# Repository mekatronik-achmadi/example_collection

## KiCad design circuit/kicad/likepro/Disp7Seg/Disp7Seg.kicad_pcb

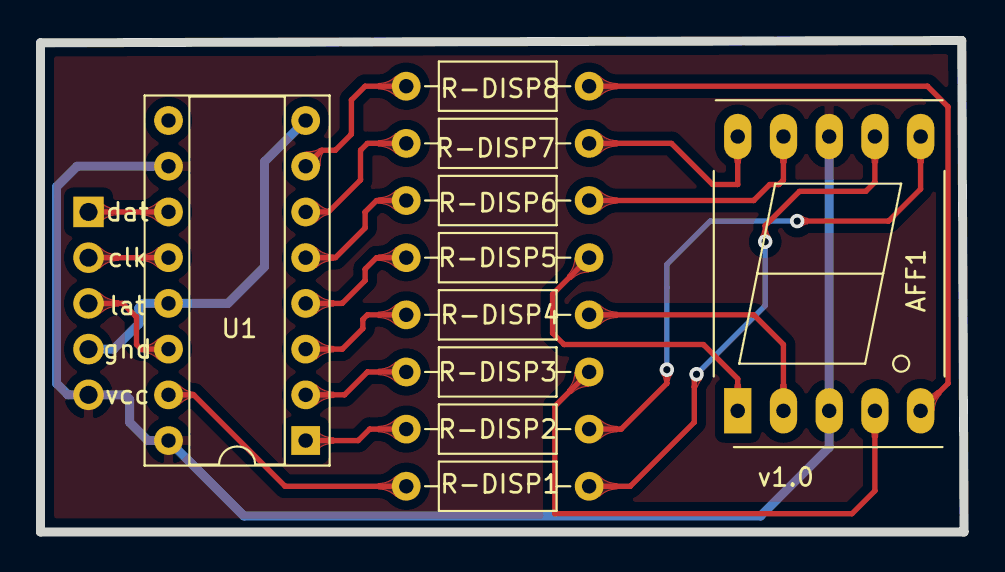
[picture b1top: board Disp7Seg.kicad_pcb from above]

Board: 2 copper layers, 51.3 x 27.3 mm, 11 parts (1 on the bottom side), 21 nets.

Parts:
AFF1: LTS-6960HR; 7SegmentLED_LTS6760_LTS6780
J-CONTROL1: Conn_01x05_Male; PinHeader_1x05_P2.54mm_Vertical
R-DISP1, R-DISP2, R-DISP3, R-DISP4, R-DISP5, R-DISP6, R-DISP7, R-DISP8: 220; R_Axial_DIN0207_L6.3mm_D2.5mm_P10.16mm_Horizontal
U1: 74HC595; DIP-16_W7.62mm_Socket

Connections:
/CLOCK: J-CONTROL1.2, U1.12
/DATA: J-CONTROL1.1, U1.11
/LATCH: J-CONTROL1.3, U1.14
/sgA: R-DISP1.2, U1.15
/sgB: R-DISP2.2, U1.1
/sgC: R-DISP3.2, U1.2
/sgD: R-DISP4.2, U1.3
/sgE: R-DISP5.2, U1.4
/sgF: R-DISP6.2, U1.5
/sgG: R-DISP7.2, U1.6
/sgH: R-DISP8.2, U1.7
GND: J-CONTROL1.4, U1.8, U1.13
unnamed: AFF1.1, R-DISP5.1
unnamed: AFF1.2, R-DISP4.1
unnamed: AFF1.4, R-DISP3.1
unnamed: AFF1.5, R-DISP8.1
unnamed: AFF1.6, R-DISP2.1
unnamed: AFF1.7, R-DISP1.1
unnamed: AFF1.9, R-DISP6.1
unnamed: AFF1.10, R-DISP7.1
VCC: AFF1.3, AFF1.8, J-CONTROL1.5, U1.10, U1.16

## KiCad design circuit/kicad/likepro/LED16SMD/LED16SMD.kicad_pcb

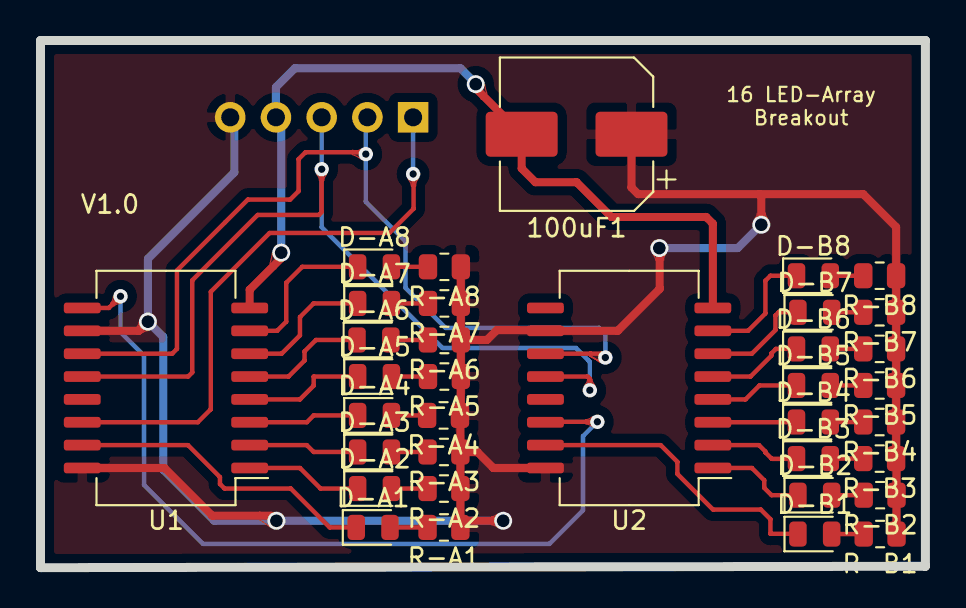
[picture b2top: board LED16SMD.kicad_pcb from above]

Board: 2 copper layers, 49.2 x 29.3 mm, 36 parts (1 on the bottom side), 38 nets.

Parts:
100uF1: CP; CP_Elec_8x5.4
D-A1, D-A2, D-A3, D-A4, D-A5, D-A6, D-A7, D-A8: LED; LED_0805_2012Metric
D-B1, D-B2, D-B3, D-B4, D-B5, D-B6, D-B7, D-B8: LED; LED_0805_2012Metric
J-CON1: Conn_01x05_Male; PinHeader_1x05_P2.54mm_Vertical
R-A1, R-A2, R-A3, R-A4, R-A5, R-A6, R-A7, R-A8: 220; R_0805_2012Metric
R-B1, R-B2, R-B3, R-B4, R-B5, R-B6, R-B7, R-B8: 220; R_0805_2012Metric
U1, U2: 74HC595; SOIC-16W_7.5x12.8mm_P1.27mm

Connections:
/CLOCK: J-CON1.2, U1.11, U2.11
/DATA: J-CON1.1, U1.14
/DATA_S: U1.9, U2.14
/LATCH: J-CON1.3, U1.12, U2.12
/saa: D-A1.1, U1.15
/sab: D-A2.1, U1.1
/sac: D-A3.1, U1.2
/sad: D-A4.1, U1.3
/sae: D-A5.1, U1.4
/saf: D-A6.1, U1.5
/sag: D-A7.1, U1.6
/sah: D-A8.1, U1.7
/sba: D-B1.1, U2.15
/sbb: D-B2.1, U2.1
/sbc: D-B3.1, U2.2
/sbd: D-B4.1, U2.3
/sbe: D-B5.1, U2.4
/sbf: D-B6.1, U2.5
/sbg: D-B7.1, U2.6
/sbh: D-B8.1, U2.7
GND: 100uF1.2, J-CON1.4, U1.8, U2.8
unnamed: D-A1.2, R-A1.2
unnamed: D-A2.2, R-A2.2
unnamed: D-A3.2, R-A3.2
unnamed: D-A4.2, R-A4.2
unnamed: D-A5.2, R-A5.2
unnamed: D-A6.2, R-A6.2
unnamed: D-A7.2, R-A7.2
unnamed: D-A8.2, R-A8.2
unnamed: D-B1.2, R-B1.2
unnamed: D-B2.2, R-B2.2
unnamed: D-B3.2, R-B3.2
unnamed: D-B4.2, R-B4.2
unnamed: D-B5.2, R-B5.2
unnamed: D-B6.2, R-B6.2
unnamed: D-B7.2, R-B7.2
unnamed: D-B8.2, R-B8.2
VCC: 100uF1.1, J-CON1.5, R-A1.1, R-A2.1, R-A3.1, R-A4.1, R-A5.1, R-A6.1, R-A7.1, R-A8.1, R-B1.1, R-B2.1, R-B3.1, R-B4.1, R-B5.1, R-B6.1, R-B7.1, R-B8.1, U1.10, U1.16, U2.10, U2.16

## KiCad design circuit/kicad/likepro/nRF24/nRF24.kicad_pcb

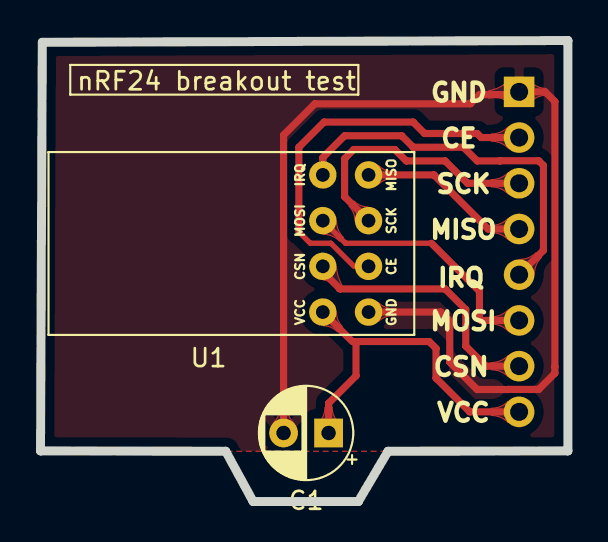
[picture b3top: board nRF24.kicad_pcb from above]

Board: 2 copper layers, 29.3 x 25.6 mm, 3 parts (1 on the bottom side), 8 nets.

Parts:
C1: 100nF; CP_Radial_D5.0mm_P2.50mm
J1: Conn_01x08_Male; PinHeader_1x08_P2.54mm_Vertical
U1: nnRF24

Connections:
/CE: J1.2, U1.1
/CSN: J1.7, U1.6
/IRQ: J1.5, U1.4
/MISO: J1.4, U1.3
/MOSI: J1.6, U1.5
/SCK: J1.3, U1.2
GND: C1.2, J1.1, U1.0
VCC: C1.1, J1.8, U1.7

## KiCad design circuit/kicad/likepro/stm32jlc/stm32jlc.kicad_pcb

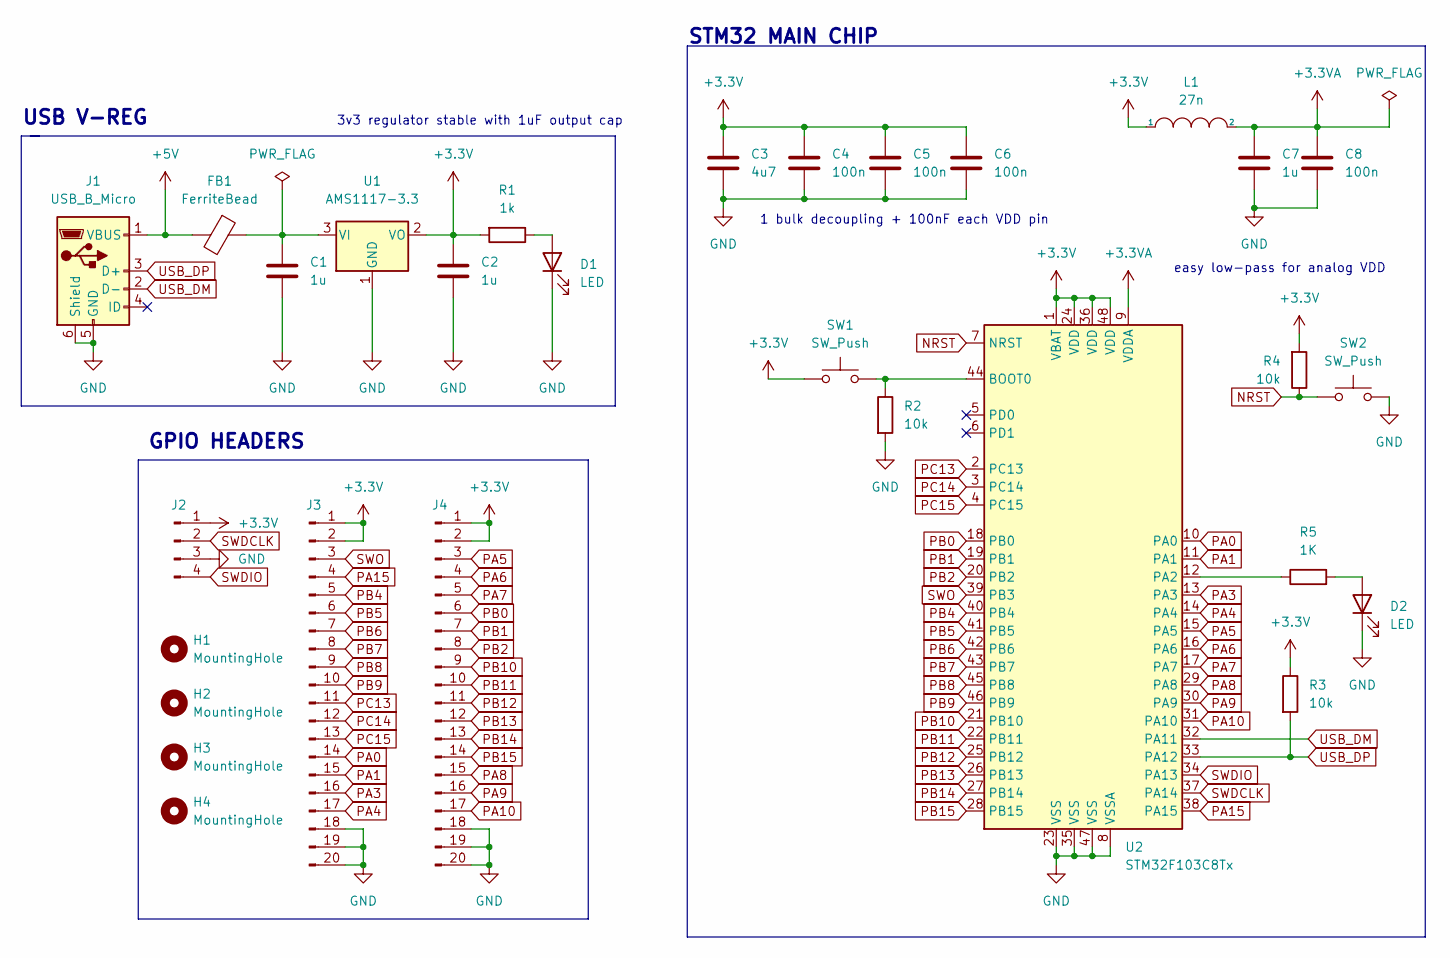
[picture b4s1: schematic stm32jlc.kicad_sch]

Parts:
C1, C2, C7: 1u; C_0805_2012Metric_Pad1.18x1.45mm_HandSolder
C3: 4u7; C_0805_2012Metric_Pad1.18x1.45mm_HandSolder
C4, C5, C6, C8: 100n; C_0805_2012Metric_Pad1.18x1.45mm_HandSolder
D1, D2: LED; LED_0805_2012Metric_Pad1.15x1.40mm_HandSolder
FB1: FerriteBead; L_0805_2012Metric_Pad1.05x1.20mm_HandSolder
H1, H2, H3, H4: MountingHole; MountingHole_2.5mm_Pad
J1: USB_B_Micro; USB_Micro-B_Wuerth_629105150521
J2: Conn_01x04_Male; PinHeader_1x04_P2.54mm_Vertical
J3, J4: Conn_01x20_Male; PinHeader_1x20_P2.54mm_Vertical
L1: 27n; L_0805_2012Metric_Pad1.05x1.20mm_HandSolder
R1: 1k; R_0805_2012Metric_Pad1.20x1.40mm_HandSolder
R2, R3, R4: 10k; R_0805_2012Metric_Pad1.20x1.40mm_HandSolder
R5: 1K; R_0805_2012Metric_Pad1.20x1.40mm_HandSolder
SW1, SW2: SW_Push; SW_PUSH_6mm
U1: AMS1117-3.3; SOT-223-3_TabPin2
U2: STM32F103C8Tx; LQFP-48_7x7mm_P0.5mm

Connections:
+3.3V: C2.1, C3.1, C4.1, C5.1, C6.1, J2.1, J3.1, J3.2, J4.1, J4.2, L1.1, R1.2, R3.1, R4.2, SW1.1, U1.2 (VO), U2.1 (VBAT), U2.24 (VDD), U2.36 (VDD), U2.48 (VDD)
+3.3VA: C7.1, C8.1, L1.2, U2.9 (VDDA)
+5V: FB1.2, J1.1 (VBUS)
GND: C1.2, C2.2, C3.2, C4.2, C5.2, C6.2, C7.2, C8.2, D1.1 (K), D2.1 (K), J1.5 (GND), J1.6 (Shield), J2.3, J3.18, J3.19, J3.20, J4.18, J4.19, J4.20, R2.2, SW2.1, U1.1 (GND), U2.8 (VSSA), U2.23 (VSS), U2.35 (VSS), U2.47 (VSS)
NRST: R4.1, SW2.2, U2.7 (NRST)
unnamed: C1.1, FB1.1, U1.3 (VI)
unnamed: D1.2 (A), R1.1
unnamed: D2.2 (A), R5.2
unnamed: R2.1, SW1.2, U2.44 (BOOT0)
unnamed: R5.1, U2.12 (PA2)
PA0: J3.14, U2.10 (PA0)
PA1: J3.15, U2.11 (PA1)
PA3: J3.16, U2.13 (PA3)
PA4: J3.17, U2.14 (PA4)
PA5: J4.3, U2.15 (PA5)
PA6: J4.4, U2.16 (PA6)
PA7: J4.5, U2.17 (PA7)
PA8: J4.15, U2.29 (PA8)
PA9: J4.16, U2.30 (PA9)
PA10: J4.17, U2.31 (PA10)
PA15: J3.4, U2.38 (PA15)
PB0: J4.6, U2.18 (PB0)
PB1: J4.7, U2.19 (PB1)
PB2: J4.8, U2.20 (PB2)
PB4: J3.5, U2.40 (PB4)
PB5: J3.6, U2.41 (PB5)
PB6: J3.7, U2.42 (PB6)
PB7: J3.8, U2.43 (PB7)
PB8: J3.9, U2.45 (PB8)
PB9: J3.10, U2.46 (PB9)
PB10: J4.9, U2.21 (PB10)
PB11: J4.10, U2.22 (PB11)
PB12: J4.11, U2.25 (PB12)
PB13: J4.12, U2.26 (PB13)
PB14: J4.13, U2.27 (PB14)
PB15: J4.14, U2.28 (PB15)
PC13: J3.11, U2.2 (PC13)
PC14: J3.12, U2.3 (PC14)
PC15: J3.13, U2.4 (PC15)
SWDCLK: J2.2, U2.37 (PA14)
SWDIO: J2.4, U2.34 (PA13)
SWO: J3.3, U2.39 (PB3)
USB_DM: J1.2 (D-), U2.32 (PA11)
USB_DP: J1.3 (D+), R3.2, U2.33 (PA12)

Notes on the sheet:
3v3 regulator stable with 1uF output cap
1 bulk decoupling + 100nF each VDD pin
STM32 MAIN CHIP
USB V-REG
easy low-pass for analog VDD
GPIO HEADERS

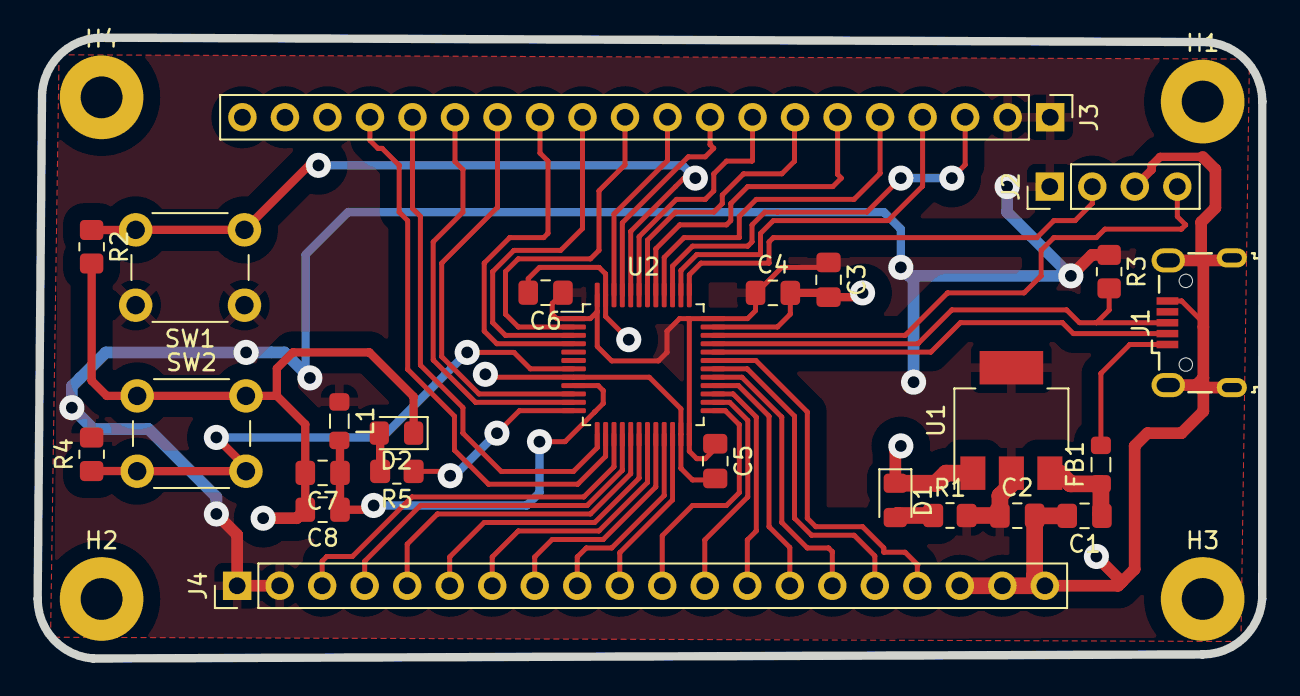
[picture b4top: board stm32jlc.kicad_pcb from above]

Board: 2 copper layers, 73.2 x 37.1 mm, 29 parts (0 on the bottom side), 44 nets.

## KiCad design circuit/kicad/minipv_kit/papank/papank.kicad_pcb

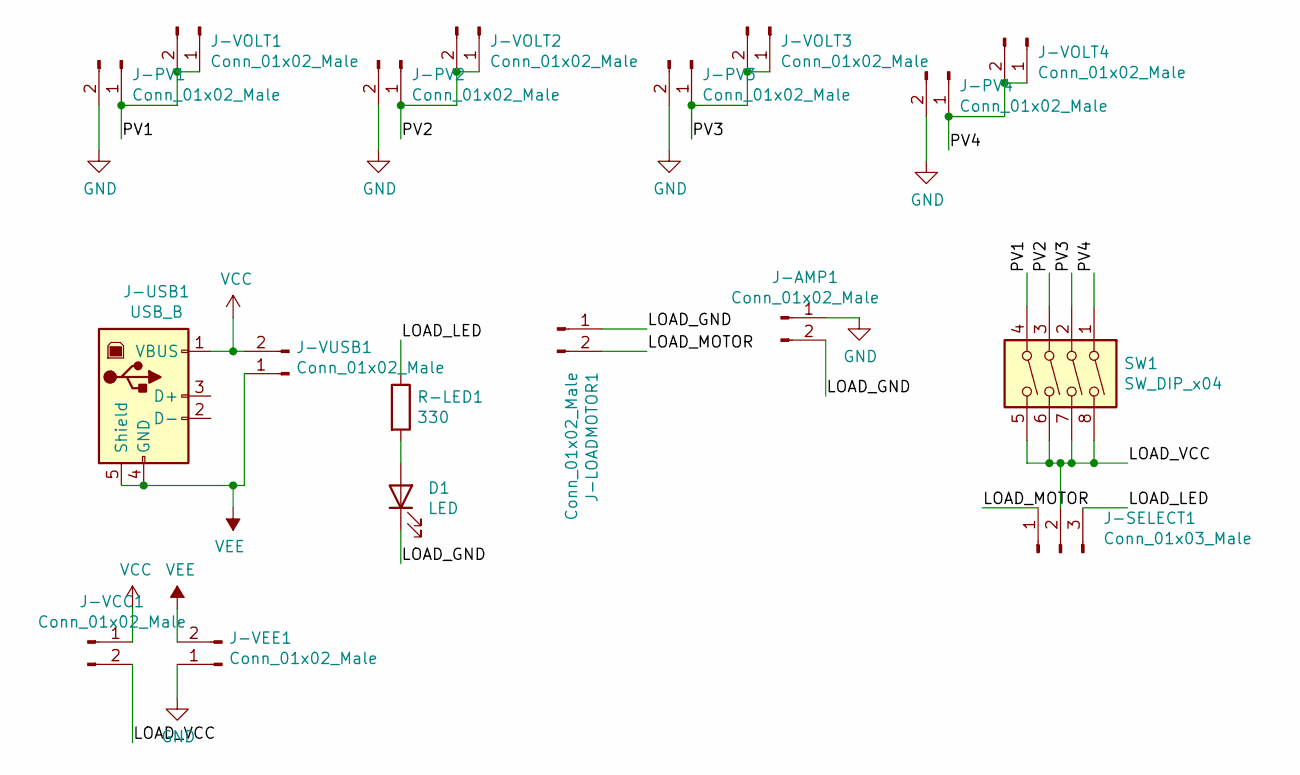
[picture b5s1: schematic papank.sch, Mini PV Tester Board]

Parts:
D1: LED; LED_D5.0mm
J-AMP1: Conn_01x02_Male; Molex_KK-254_AE-6410-02A_1x02_P2.54mm_Vertical
J-LOADMOTOR1: Conn_01x02_Male; Molex_KK-254_AE-6410-02A_1x02_P2.54mm_Vertical
J-PV1, J-PV2, J-PV3, J-PV4: Conn_01x02_Male; Molex_KK-254_AE-6410-02A_1x02_P2.54mm_Vertical
J-SELECT1: Conn_01x03_Male; PinHeader_1x03_P2.54mm_Vertical
J-USB1: USB_B; USB_B_Lumberg_2411_02_Horizontal
J-VCC1: Conn_01x02_Male; PinHeader_1x02_P2.54mm_Vertical
J-VEE1: Conn_01x02_Male; PinHeader_1x02_P2.54mm_Vertical
J-VOLT1, J-VOLT2, J-VOLT3, J-VOLT4: Conn_01x02_Male; PinHeader_1x02_P2.54mm_Vertical
J-VUSB1: Conn_01x02_Male; PinHeader_1x02_P2.54mm_Vertical
R-LED1: 330; R_Axial_DIN0207_L6.3mm_D2.5mm_P10.16mm_Horizontal
SW1: SW_DIP_x04; SW_DIP_SPSTx04_Slide_9.78x12.34mm_W7.62mm_P2.54mm

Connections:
/LOAD_GND: D1.1 (K), J-AMP1.2, J-LOADMOTOR1.1
/LOAD_LED: J-SELECT1.3, R-LED1.1
/LOAD_MOTOR: J-LOADMOTOR1.2, J-SELECT1.1
/LOAD_VCC: J-SELECT1.2, J-VCC1.2, SW1.5, SW1.6, SW1.7, SW1.8
/PV1: J-PV1.1, J-VOLT1.1, J-VOLT1.2, SW1.4
/PV2: J-PV2.1, J-VOLT2.1, J-VOLT2.2, SW1.3
/PV3: J-PV3.1, J-VOLT3.1, J-VOLT3.2, SW1.2
/PV4: J-PV4.1, J-VOLT4.1, J-VOLT4.2, SW1.1
GND: J-AMP1.1, J-PV1.2, J-PV2.2, J-PV3.2, J-PV4.2, J-VEE1.1
unnamed: D1.2 (A), R-LED1.2
VCC: J-USB1.1 (VBUS), J-VCC1.1, J-VUSB1.2
VEE: J-USB1.4 (GND), J-USB1.5 (Shield), J-VEE1.2, J-VUSB1.1

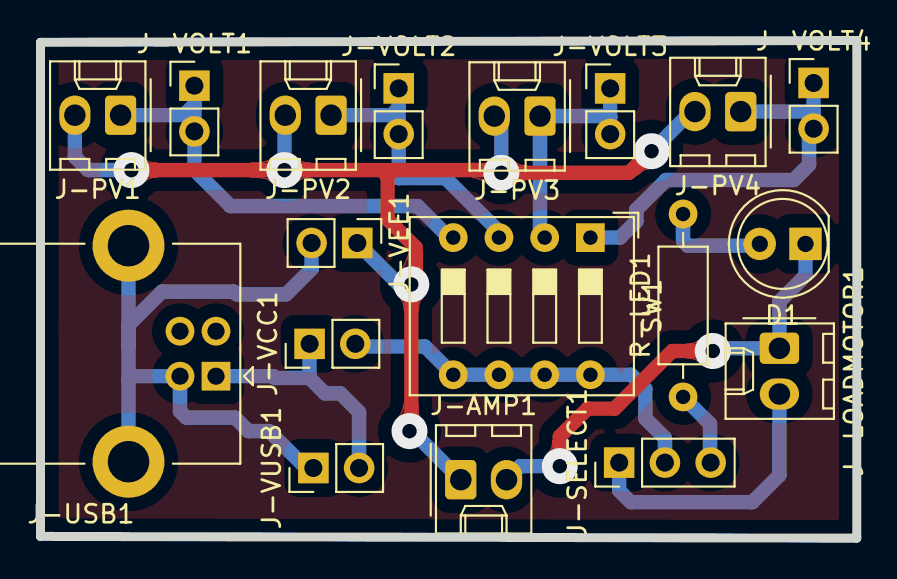
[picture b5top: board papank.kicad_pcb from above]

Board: 2 copper layers, 45.3 x 27.7 mm, 18 parts (0 on the bottom side), 12 nets.

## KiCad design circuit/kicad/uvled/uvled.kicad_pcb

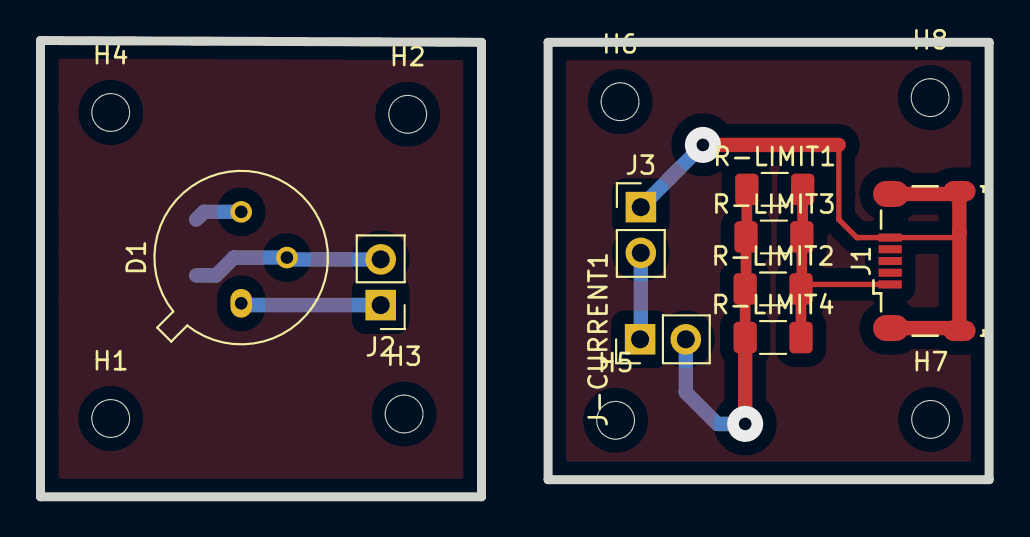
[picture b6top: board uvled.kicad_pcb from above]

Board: 2 copper layers, 52.7 x 25.4 mm, 18 parts (1 on the bottom side), 5 nets.

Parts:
D1: LED_PAD; TO-39-3
H1, H2, H3, H4, H5, H6, H7, H8: MountingHole; MountingHole_2.1mm
J1: USB_B_Micro; MicroUSB
J2, J3: Conn_01x02_Male; PinHeader_1x02_P2.54mm_Vertical
J-CURRENT1: Conn_01x02_Male; PinHeader_1x02_P2.54mm_Vertical
R-GND1: 0; R_1206_3216Metric_Pad1.30x1.75mm_HandSolder
R-LIMIT1, R-LIMIT2, R-LIMIT3, R-LIMIT4: 10K; R_1206_3216Metric_Pad1.30x1.75mm_HandSolder

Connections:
/VLED: D1.1, J2.1, J3.2, J-CURRENT1.1
GND: D1.2, J1.5, J1.6, J2.2, J3.1, R-GND1.2
unnamed: D1.3, R-GND1.1
unnamed: J-CURRENT1.2, R-LIMIT1.1, R-LIMIT2.1, R-LIMIT3.1, R-LIMIT4.1
VCC: J1.1, R-LIMIT1.2, R-LIMIT2.2, R-LIMIT3.2, R-LIMIT4.2

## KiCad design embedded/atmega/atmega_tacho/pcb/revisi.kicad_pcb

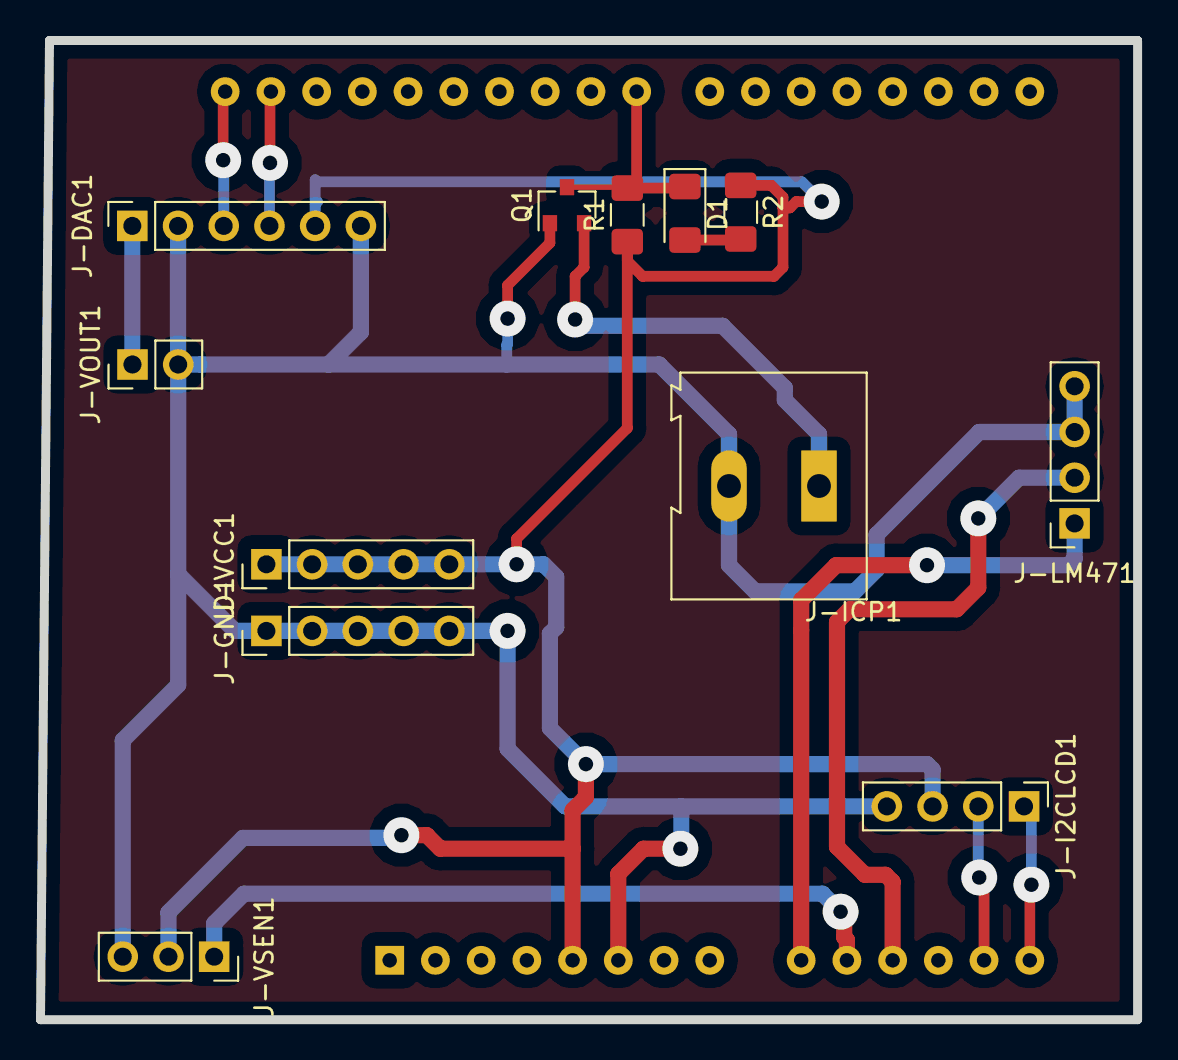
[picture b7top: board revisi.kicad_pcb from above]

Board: 2 copper layers, 60.9 x 54.4 mm, 13 parts (1 on the bottom side), 13 nets.

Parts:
A1: Arduino_UNO_R3
D1: LED; LED_1206_3216Metric_Pad1.42x1.75mm_HandSolder
J-DAC1: Conn_01x06_Male; PinSocket_1x06_P2.54mm_Vertical
J-GND1: Conn_01x05_Male; PinHeader_1x05_P2.54mm_Vertical
J-I2CLCD1: Conn_01x04_Male; PinHeader_1x04_P2.54mm_Vertical
J-ICP1: Conn_01x02_Male; TerminalBlock_Altech_AK300-2_P5.00mm
J-LM471: Conn_01x04_Male; PinSocket_1x04_P2.54mm_Vertical
J-VCC1: Conn_01x05_Male; PinHeader_1x05_P2.54mm_Vertical
J-VOUT1: Conn_01x02_Male; PinHeader_1x02_P2.54mm_Vertical
J-VSEN1: Conn_01x03_Male; PinSocket_1x03_P2.54mm_Vertical
Q1: 2N3904; SOT-23
R1: 4k7; R_1206_3216Metric_Pad1.42x1.75mm_HandSolder
R2: 330; R_1206_3216Metric_Pad1.42x1.75mm_HandSolder

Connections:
/ADC0: A1.9, J-LM471.1
/ADC1: A1.10, J-VSEN1.1
/ADC2: A1.11, J-LM471.2
/ICP: A1.23, D1.1, Q1.3, R1.2
/SCL1: A1.14, J-I2CLCD1.1
/SCL2: A1.32, J-DAC1.3
/SDA1: A1.13, J-I2CLCD1.2
/SDA2: A1.31, J-DAC1.4
GND: A1.6, J-DAC1.2, J-DAC1.6, J-GND1.1, J-GND1.2, J-GND1.3, J-GND1.4, J-GND1.5, J-I2CLCD1.4, J-ICP1.2, J-LM471.3, J-LM471.4, J-VOUT1.2, J-VSEN1.3, Q1.1
unnamed: D1.2, R2.2
unnamed: J-DAC1.1, J-VOUT1.1
unnamed: J-ICP1.1, Q1.2
VCC: A1.5, J-DAC1.5, J-I2CLCD1.3, J-VCC1.1, J-VCC1.2, J-VCC1.3, J-VCC1.4, J-VCC1.5, J-VSEN1.2, R1.1, R2.1

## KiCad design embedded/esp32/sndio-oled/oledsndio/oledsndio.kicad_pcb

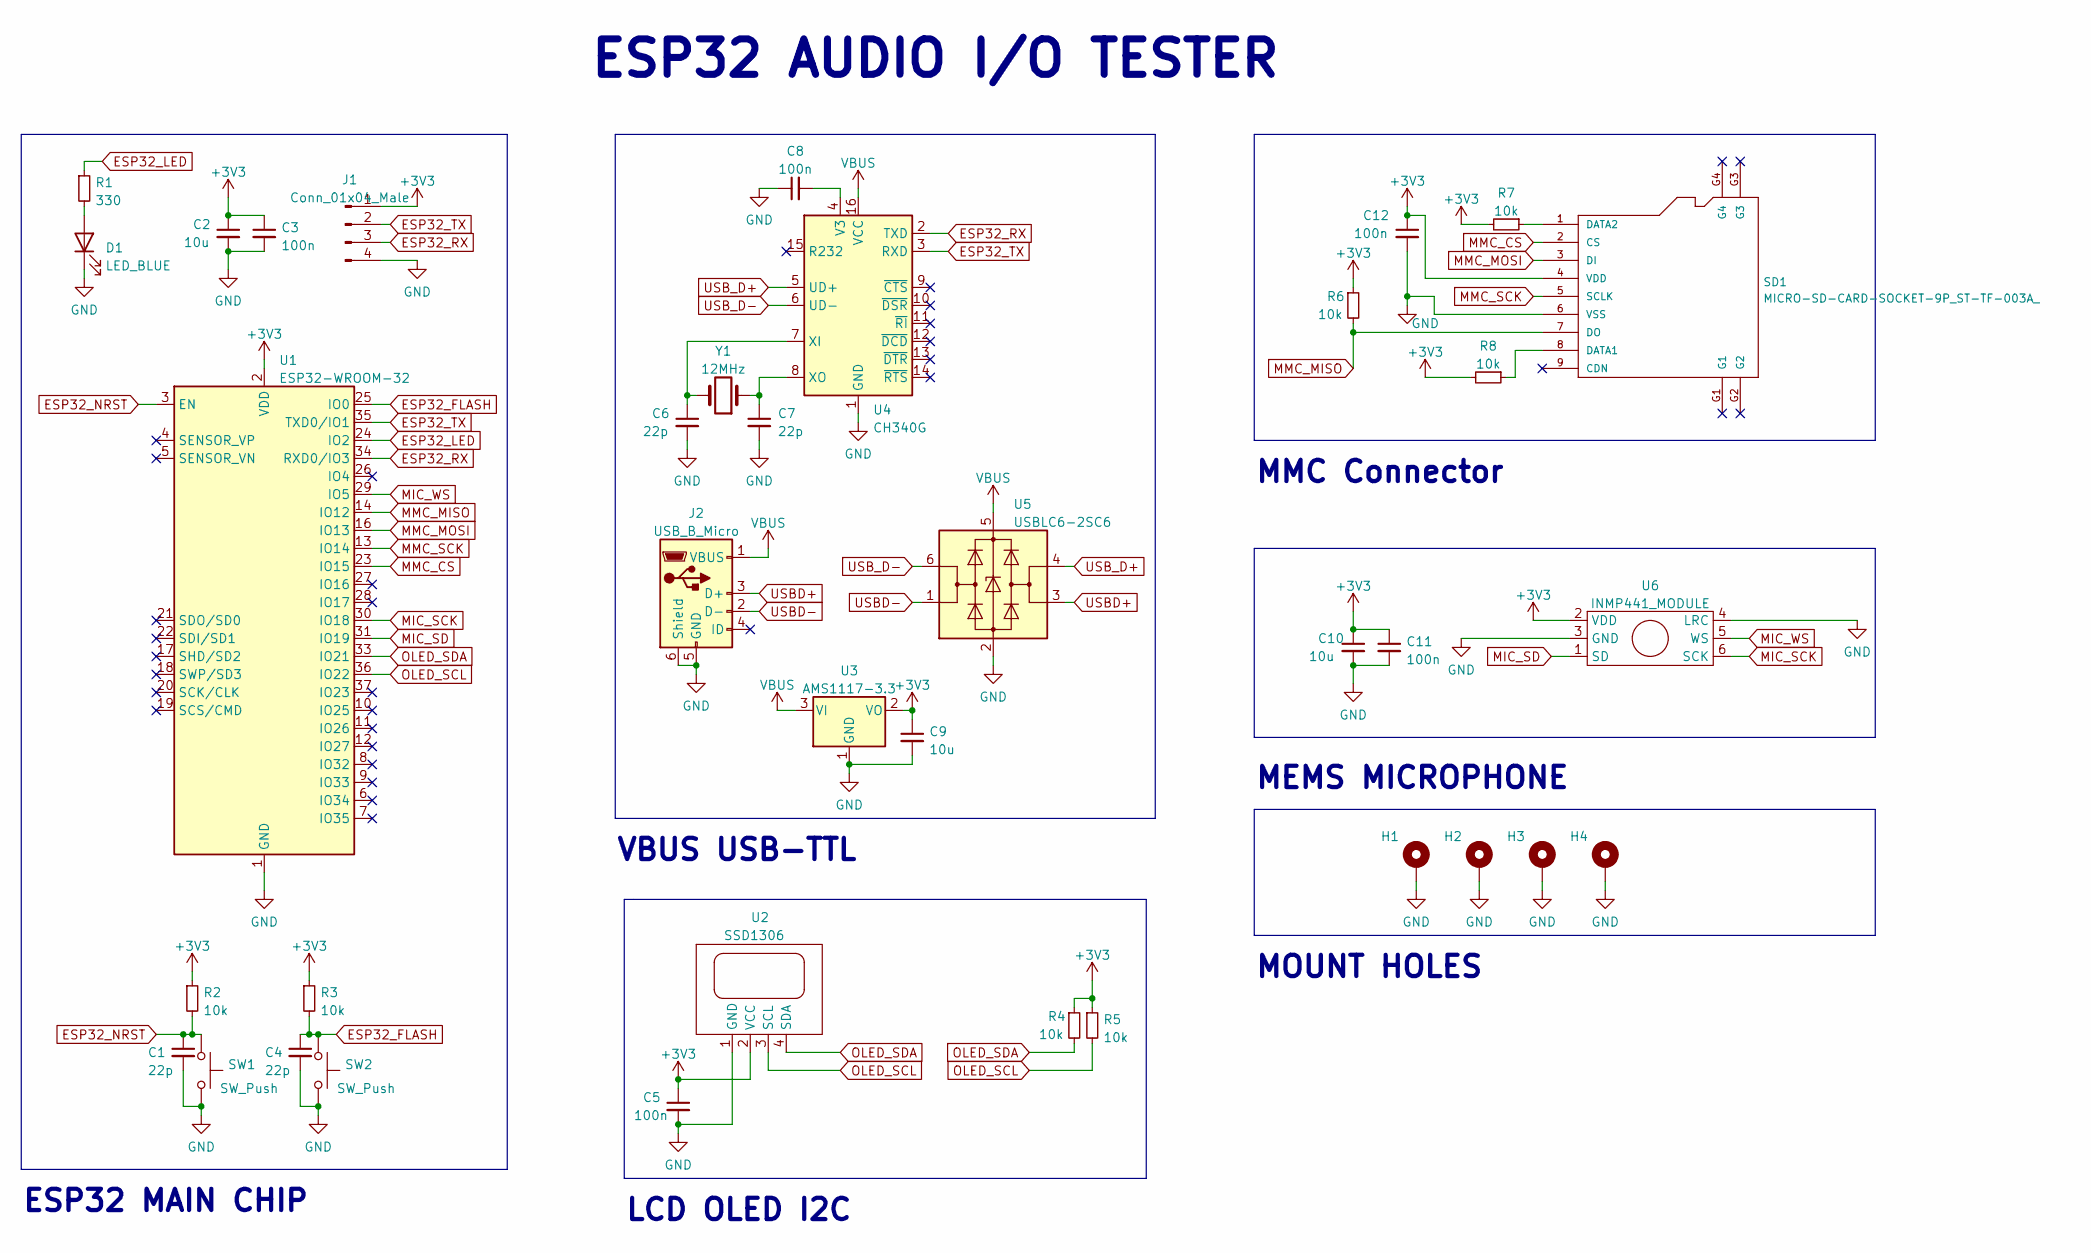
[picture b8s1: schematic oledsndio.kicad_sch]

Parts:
C1, C4, C6, C7: 22p; C_0805_2012Metric_Pad1.18x1.45mm_HandSolder
C2, C9, C10: 10u; C_0805_2012Metric_Pad1.18x1.45mm_HandSolder
C3, C5, C8, C11, C12: 100n; C_0805_2012Metric_Pad1.18x1.45mm_HandSolder
D1: LED_BLUE; LED_0805_2012Metric_Pad1.15x1.40mm_HandSolder
H1, H2, H3, H4: MountingHole_Pad; MountingHole_5.3mm_M5_Pad
J1: Conn_01x04_Male; PinHeader_1x04_P2.54mm_Vertical
J2: USB_B_Micro; USB_Micro-B_Wuerth_629105150521
R1: 330; R_0805_2012Metric_Pad1.20x1.40mm_HandSolder
R2, R3, R4, R5, R6, R7, R8: 10k; R_0805_2012Metric_Pad1.20x1.40mm_HandSolder
SD1: MICRO-SD-CARD-SOCKET-9P_ST-TF-003A_; MICRO-SD9+4P-SMD-16.1X14.5X1.85MM; MPN ST-TF-003A
SW1, SW2: SW_Push; SW_PUSH_6mm
U1: ESP32-WROOM-32
U2: SSD1306; Display_128x64_096_I2C
U3: AMS1117-3.3; SOT-223-3_TabPin2
U4: CH340G; SOIC-16_3.9x9.9mm_P1.27mm
U5: USBLC6-2SC6; SOT-23-6
U6: INMP441_MODULE; INMP441
Y1: 12MHz; Crystal_SMD_HC49-SD_HandSoldering

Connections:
+3V3: C2.1, C3.1, C5.1, C9.1, C10.1, C11.1, C12.1, J1.1, R2.1, R3.1, R4.1, R5.1, R6.1, R7.2, R8.2, SD1.4 (VDD), U1.2 (VDD), U2.2 (VCC), U3.2 (VO), U6.2 (VDD)
ESP32_FLASH: C4.1, R3.2, SW2.1, U1.25 (IO0)
ESP32_LED: R1.1, U1.24 (IO2)
ESP32_NRST: C1.1, R2.2, SW1.1, U1.3 (EN)
ESP32_RX: J1.3, U1.34 (RXD0/IO3), U4.2 (TXD)
ESP32_TX: J1.2, U1.35 (TXD0/IO1), U4.3 (RXD)
GND: C1.2, C2.2, C3.2, C4.2, C5.2, C6.2, C7.2, C8.1, C9.2, C10.2, C11.2, C12.2, D1.1 (K), H1.1, H2.1, H3.1, H4.1, J1.4, J2.5 (GND), J2.6 (Shield), SD1.6 (VSS), SW1.2, SW2.2, U1.1 (GND), U1.15 (GND), U1.38 (GND), U1.39 (GND), U2.1 (GND), U3.1 (GND), U4.1 (GND), U5.2 (GND), U6.3 (GND), U6.4 (LRC)
MIC_SCK: U1.30 (IO18), U6.6 (SCK)
MIC_SD: U1.31 (IO19), U6.1 (SD)
MIC_WS: U1.29 (IO5), U6.5 (WS)
MMC_CS: SD1.2 (CS), U1.23 (IO15)
MMC_MISO: R6.2, SD1.7 (DO), U1.14 (IO12)
MMC_MOSI: SD1.3 (DI), U1.16 (IO13)
MMC_SCK: SD1.5 (SCLK), U1.13 (IO14)
unnamed: C6.1, U4.7 (XI), Y1.2
unnamed: C7.1, U4.8 (XO), Y1.1
unnamed: C8.2, U4.4 (V3)
unnamed: D1.2 (A), R1.2
unnamed: R7.1, SD1.1 (DATA2)
unnamed: R8.1, SD1.8 (DATA1)
OLED_SCL: R5.2, U1.36 (IO22), U2.3 (SCL)
OLED_SDA: R4.2, U1.33 (IO21), U2.4 (SDA)
USBD+: J2.3 (D+), U5.3 (I/O2)
USBD-: J2.2 (D-), U5.1 (I/O1)
USB_D+: U4.5 (UD+), U5.4 (I/O2)
USB_D-: U4.6 (UD-), U5.6 (I/O1)
VBUS: J2.1 (VBUS), U3.3 (VI), U4.16 (VCC), U5.5 (VBUS)

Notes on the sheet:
VBUS USB-TTL
ESP32 AUDIO I/O TESTER
MEMS MICROPHONE
MOUNT HOLES
MMC Connector
ESP32 MAIN CHIP
LCD OLED I2C

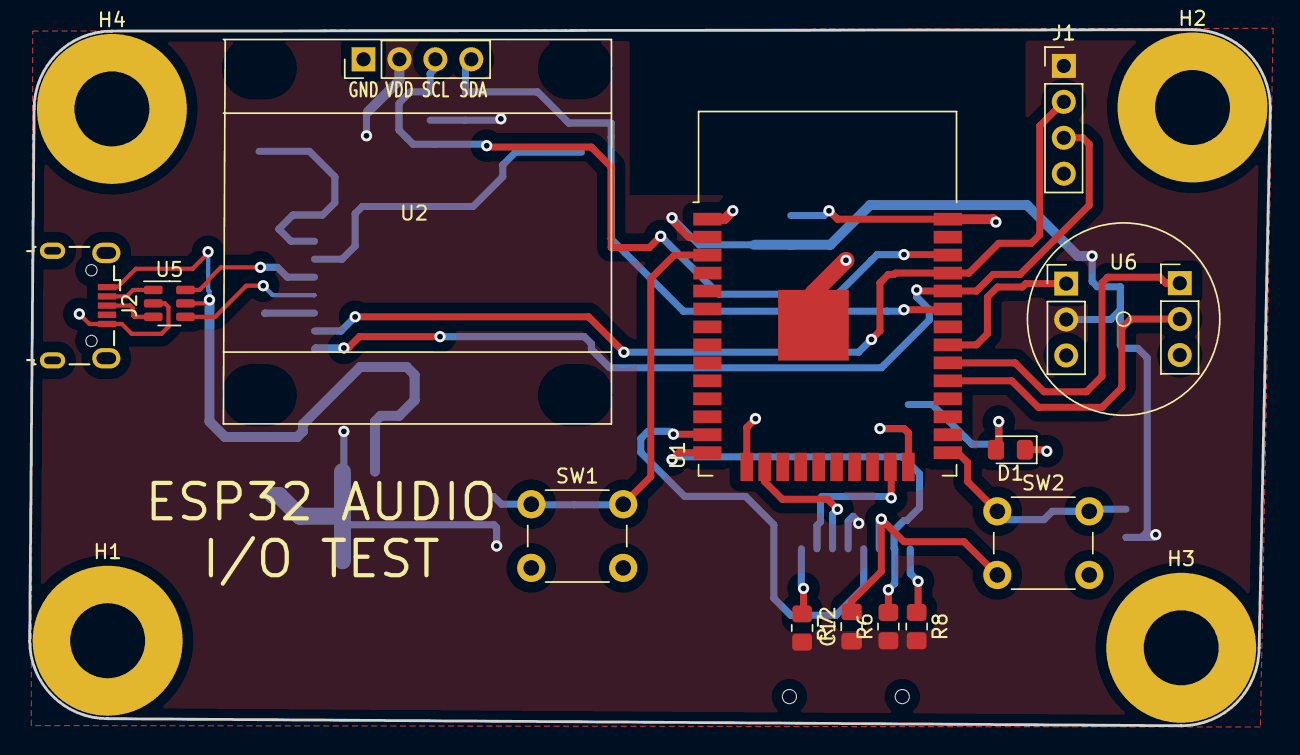
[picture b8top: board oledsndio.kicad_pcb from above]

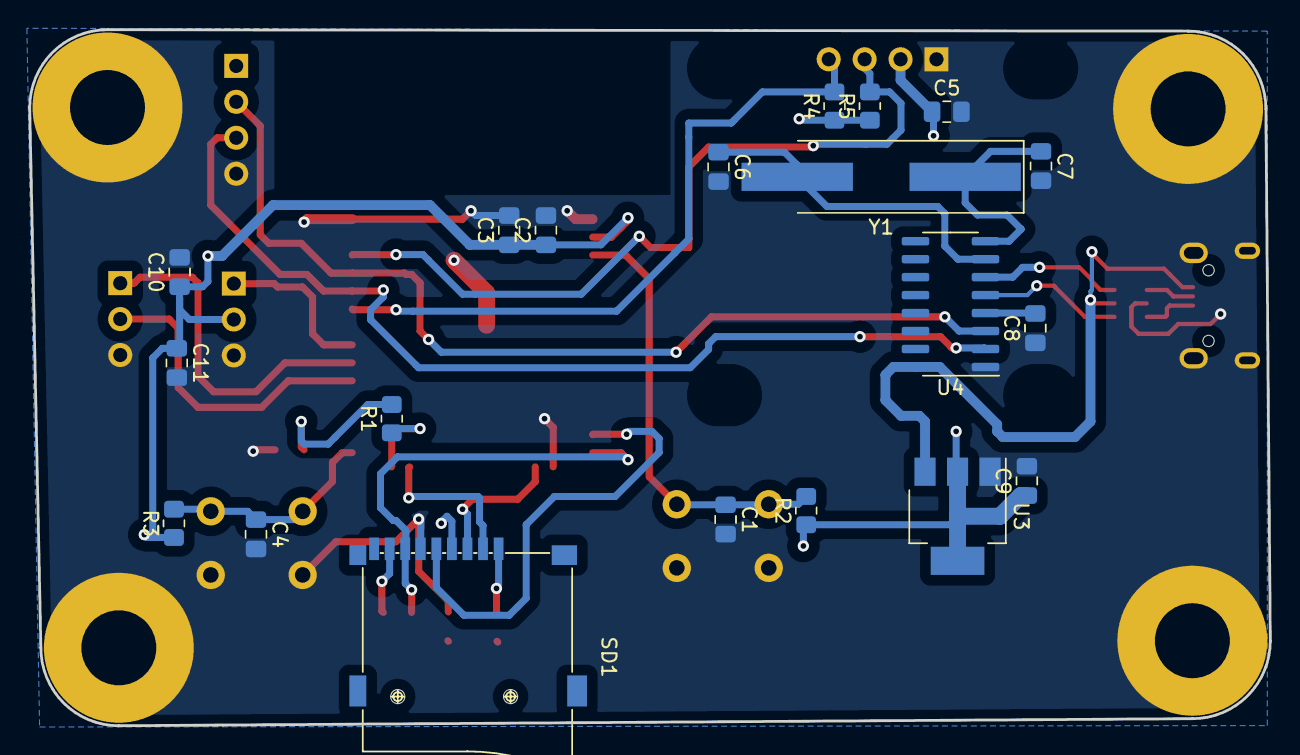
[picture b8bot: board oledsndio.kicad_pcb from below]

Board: 2 copper layers, 87.7 x 49.2 mm, 37 parts (20 on the bottom side), 27 nets.
